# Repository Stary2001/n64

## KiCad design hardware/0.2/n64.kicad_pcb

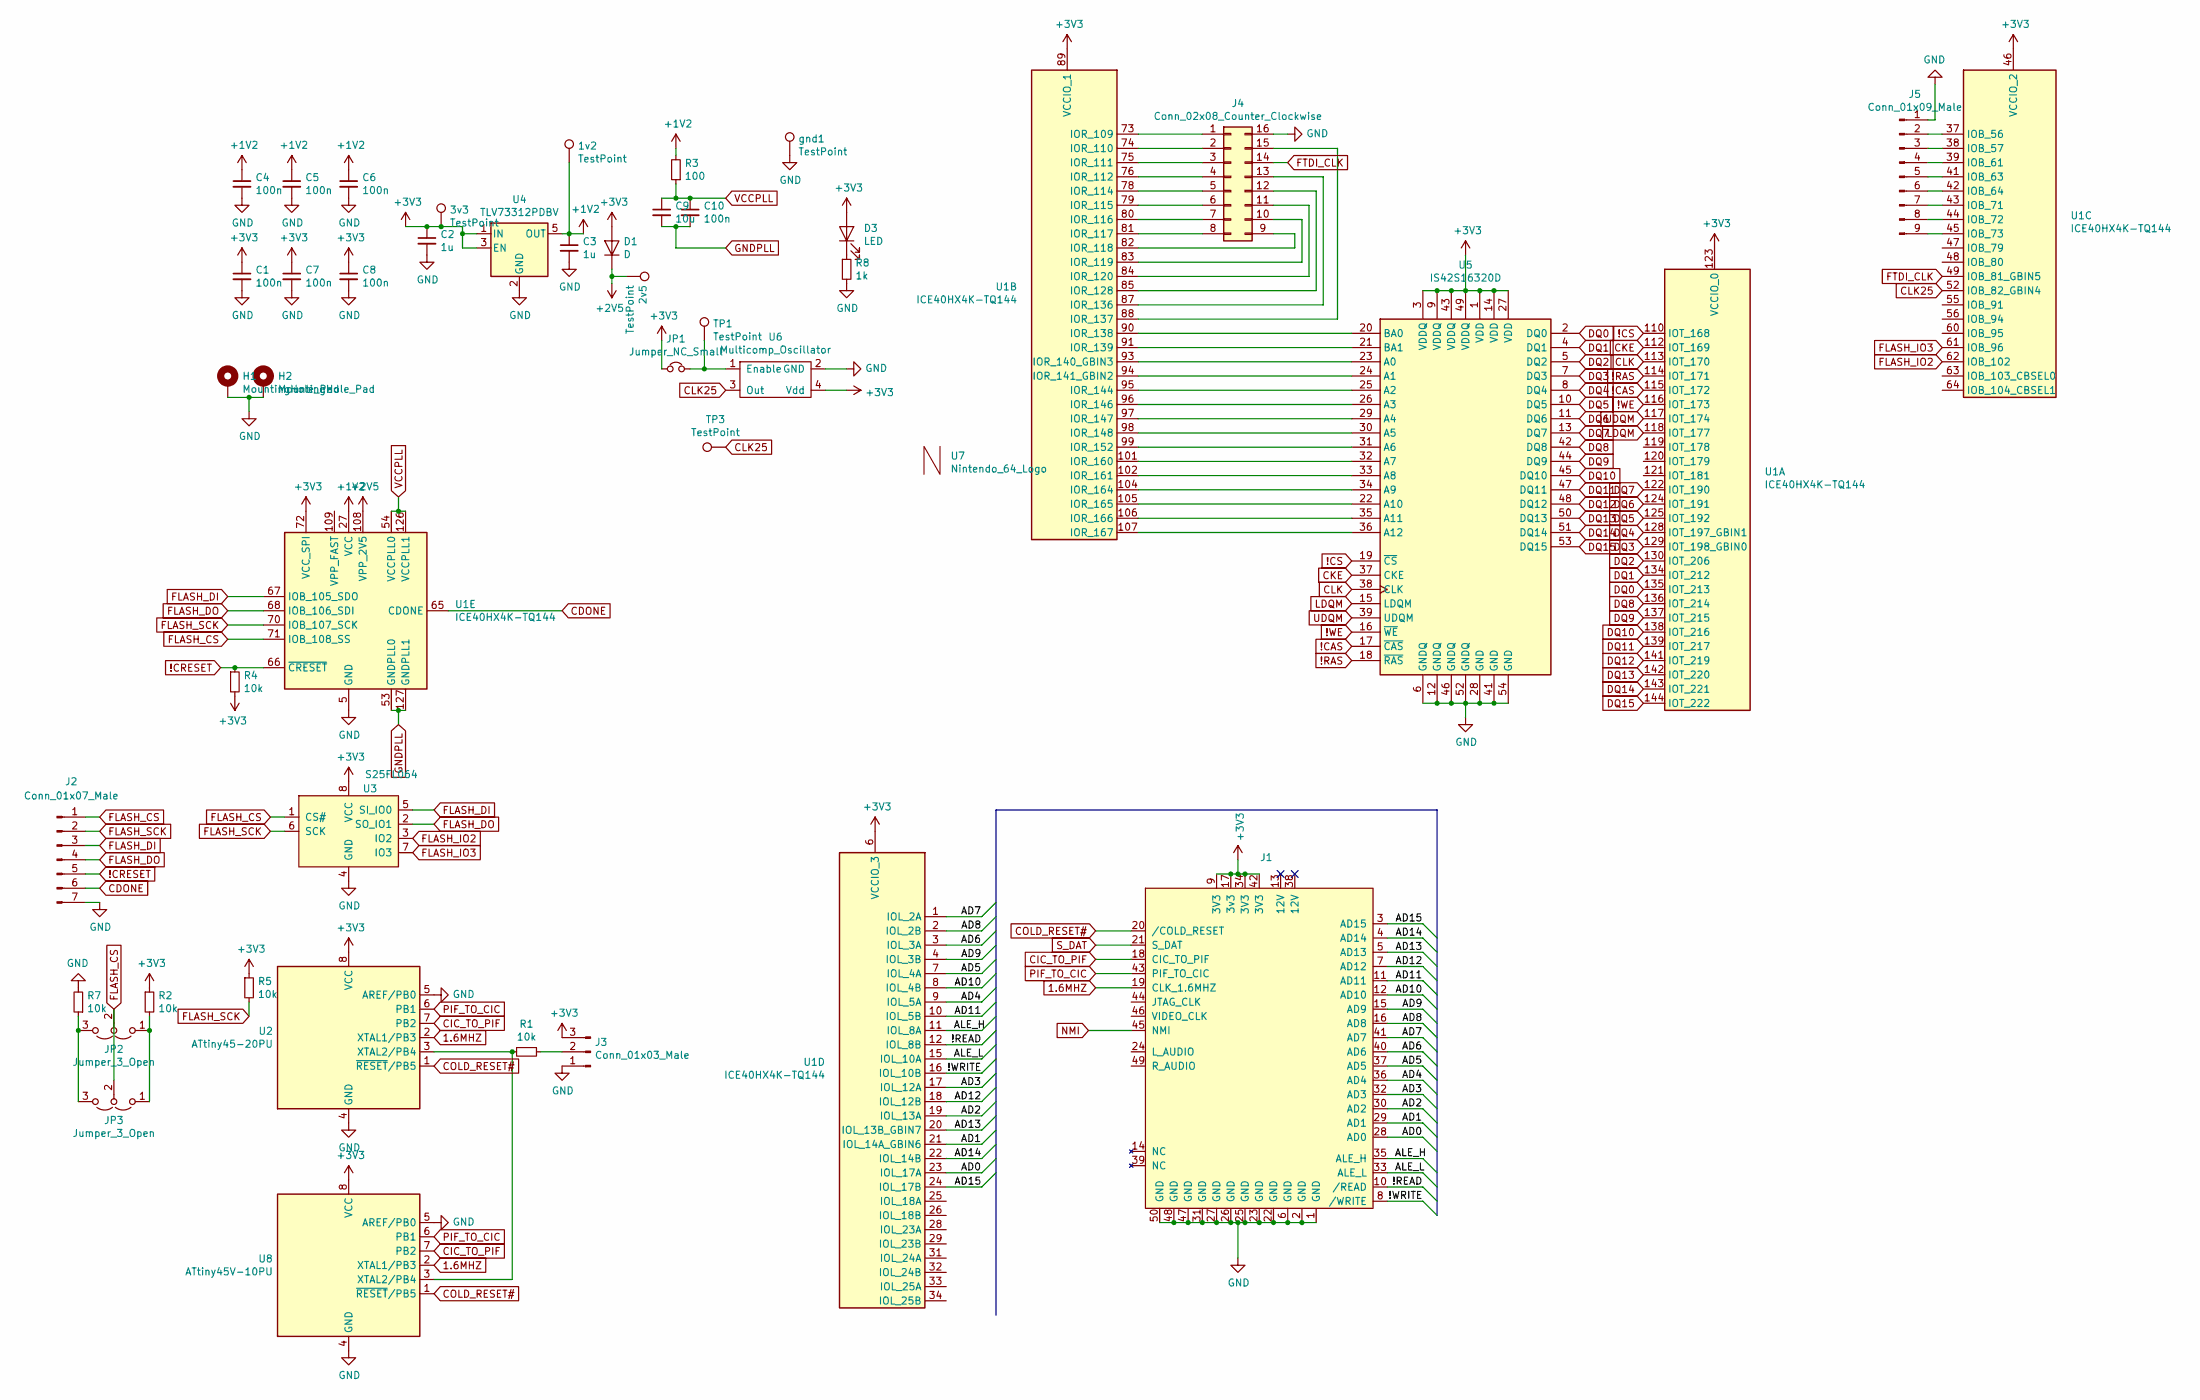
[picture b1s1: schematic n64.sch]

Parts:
1v2, 2v5, 3v3: TestPoint; TestPoint_Pad_D2.5mm
C1, C4, C5, C6, C7, C8, C10: 100n; R_0603_1608Metric_Pad1.05x0.95mm_HandSolder
C2, C3: 1u; R_0603_1608Metric_Pad1.05x0.95mm_HandSolder
C9: 10u; R_0603_1608Metric_Pad1.05x0.95mm_HandSolder
D1: D; D_SOD-123
D3: LED; LED_0603_1608Metric_Pad1.05x0.95mm_HandSolder
H1, H2: MountingHole_Pad; MountingHole_2.7mm_M2.5_Pad
J1: Nintendo_64_Cartridge
J2: Conn_01x07_Male; PinHeader_1x07_P2.54mm_Vertical
J3: Conn_01x03_Male; PinHeader_1x03_P2.54mm_Vertical
J4: Conn_02x08_Counter_Clockwise; IDC-Header_2x08_P2.54mm_Vertical
J5: Conn_01x09_Male; PinHeader_1x09_P2.54mm_Vertical
JP1: Jumper_NC_Small; SolderJumper-2_P1.3mm_Bridged_RoundedPad1.0x1.5mm
JP2: Jumper_3_Open; PinHeader_1x03_P2.54mm_Vertical
JP3: Jumper_3_Open; SolderJumper-3_P1.3mm_Open_Pad1.0x1.5mm_NumberLabels
R1, R2, R4, R5, R7: 10k; R_0603_1608Metric_Pad1.05x0.95mm_HandSolder
R3: 100; R_0603_1608Metric_Pad1.05x0.95mm_HandSolder
R8: 1k; R_0603_1608Metric_Pad1.05x0.95mm_HandSolder
TP1, TP3: TestPoint; TestPoint_Pad_D1.5mm
U1: ICE40HX4K-TQ144; TQFP-144_20x20mm_P0.5mm
U2: ATtiny45-20PU; DIP-8_W7.62mm
U3: S25FL064; SOIC-8_5.23x5.23mm_P1.27mm
U4: TLV73312PDBV; SOT-23-5
U5: IS42S16320D; TSOP-II-54_22.2x10.16mm_P0.8mm
U6: Multicomp_Oscillator; Oscillator_SMD_Abracon_ASE-4Pin_3.2x2.5mm
U7: Nintendo_64_Logo
U8: ATtiny45V-10PU; SOIC-8_5.23x5.23mm_P1.27mm
gnd1: TestPoint; TestPoint_Pad_D2.5mm

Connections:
1.6MHZ: J1.19 (CLK_1.6MHZ), U2.2 (XTAL1/PB3), U8.2 (XTAL1/PB3)
!CAS: U1.115 (IOT_172), U5.17 (~CAS)
!CRESET: J2.5, R4.1, U1.66 (~CRESET)
!CS: U1.110 (IOT_168), U5.19 (~CS)
!RAS: U1.114 (IOT_171), U5.18 (~RAS)
!WE: U1.116 (IOT_173), U5.16 (~WE)
+1V2: 1v2.1, C3.1, C4.1, C5.1, C6.1, R3.2, U1.27 (VCC), U1.40 (VCC), U1.92 (VCC), U1.111 (VCC), U4.5 (OUT)
+2V5: 2v5.1, D1.1 (K), U1.108 (VPP_2V5)
+3V3: 3v3.1, C1.1, C2.1, C7.1, C8.1, D1.2 (A), D3.2 (A), J1.9 (3V3), J1.17 (3v3), J1.34 (3V3), J1.42 (3V3), J3.3, JP1.1, R2.1, R4.2, R5.1, U1.6 (VCCIO_3), U1.30 (VCCIO_3), U1.46 (VCCIO_2), U1.57 (VCCIO_2), U1.72 (VCC_SPI), U1.89 (VCCIO_1), U1.100 (VCCIO_1), U1.123 (VCCIO_0), U1.131 (VCCIO_0), U2.8 (VCC), U3.8 (VCC), U4.1 (IN), U4.3 (EN), U5.1 (VDD), U5.3 (VDDQ), U5.9 (VDDQ), U5.14 (VDD), U5.27 (VDD), U5.43 (VDDQ), U5.49 (VDDQ), U6.4 (Vdd), U8.8 (VCC)
/!READ: J1.10 (/READ), U1.12 (IOL_8B)
/!WRITE: J1.8 (/WRITE), U1.16 (IOL_10B)
/AD0: J1.28 (AD0), U1.23 (IOL_17A)
/AD1: J1.29 (AD1), U1.21 (IOL_14A_GBIN6)
/AD2: J1.30 (AD2), U1.19 (IOL_13A)
/AD3: J1.32 (AD3), U1.17 (IOL_12A)
/AD4: J1.36 (AD4), U1.9 (IOL_5A)
/AD5: J1.37 (AD5), U1.7 (IOL_4A)
/AD6: J1.40 (AD6), U1.3 (IOL_3A)
/AD7: J1.41 (AD7), U1.1 (IOL_2A)
/AD8: J1.16 (AD8), U1.2 (IOL_2B)
/AD9: J1.15 (AD9), U1.4 (IOL_3B)
/AD10: J1.12 (AD10), U1.8 (IOL_4B)
/AD11: J1.11 (AD11), U1.10 (IOL_5B)
/AD12: J1.7 (AD12), U1.18 (IOL_12B)
/AD13: J1.5 (AD13), U1.20 (IOL_13B_GBIN7)
/AD14: J1.4 (AD14), U1.22 (IOL_14B)
/AD15: J1.3 (AD15), U1.24 (IOL_17B)
/ALE_H: J1.35 (ALE_H), U1.11 (IOL_8A)
/ALE_L: J1.33 (ALE_L), U1.15 (IOL_10A)
CDONE: J2.6, U1.65 (CDONE)
CIC_TO_PIF: J1.18 (CIC_TO_PIF), U2.7 (PB2), U8.7 (PB2)
CKE: U1.112 (IOT_169), U5.37 (CKE)
CLK: U1.113 (IOT_170), U5.38 (CLK)
CLK25: TP3.1, U1.52 (IOB_82_GBIN4), U6.3 (Out)
COLD_RESET#: J1.20 (/COLD_RESET), U2.1 (~RESET~/PB5), U8.1 (~RESET~/PB5)
DQ0: U1.135 (IOT_213), U5.2 (DQ0)
DQ1: U1.134 (IOT_212), U5.4 (DQ1)
DQ2: U1.130 (IOT_206), U5.5 (DQ2)
DQ3: U1.129 (IOT_198_GBIN0), U5.7 (DQ3)
DQ4: U1.128 (IOT_197_GBIN1), U5.8 (DQ4)
DQ5: U1.125 (IOT_192), U5.10 (DQ5)
DQ6: U1.124 (IOT_191), U5.11 (DQ6)
DQ7: U1.122 (IOT_190), U5.13 (DQ7)
DQ8: U1.136 (IOT_214), U5.42 (DQ8)
DQ9: U1.137 (IOT_215), U5.44 (DQ9)
DQ10: U1.138 (IOT_216), U5.45 (DQ10)
DQ11: U1.139 (IOT_217), U5.47 (DQ11)
DQ12: U1.141 (IOT_219), U5.48 (DQ12)
DQ13: U1.142 (IOT_220), U5.50 (DQ13)
DQ14: U1.143 (IOT_221), U5.51 (DQ14)
DQ15: U1.144 (IOT_222), U5.53 (DQ15)
FLASH_CS: J2.1, JP2.2 (C), JP3.2 (C), U1.71 (IOB_108_SS), U3.1 (CS#)
FLASH_DI: J2.3, U1.67 (IOB_105_SDO), U3.5 (SI_IO0)
FLASH_DO: J2.4, U1.68 (IOB_106_SDI), U3.2 (SO_IO1)
FLASH_IO2: U1.62 (IOB_102), U3.3 (IO2)
FLASH_IO3: U1.61 (IOB_96), U3.7 (IO3)
FLASH_SCK: J2.2, R5.2, U1.70 (IOB_107_SCK), U3.6 (SCK)
FTDI_CLK: J4.14, U1.49 (IOB_81_GBIN5)
GND: C1.2, C2.2, C3.2, C4.2, C5.2, C6.2, C7.2, C8.2, H1.1, H2.1, J1.1 (GND), J1.2 (GND), J1.6 (GND), J1.22 (GND), J1.23 (GND), J1.25 (GND), J1.26 (GND), J1.27 (GND), J1.31 (GND), J1.47 (GND), J1.48 (GND), J1.50 (GND), J2.7, J3.1, J4.16, J5.1, R7.2, R8.2, U1.5 (GND), U1.13 (GND), U1.14 (GND), U1.59 (GND), U1.69 (GND), U1.86 (GND), U1.103 (GND), U1.132 (GND), U1.140 (GND), U2.4 (GND), U2.5 (AREF/PB0), U3.4 (GND), U4.2 (GND), U5.6 (GNDQ), U5.12 (GNDQ), U5.28 (GND), U5.41 (GND), U5.46 (GNDQ), U5.52 (GNDQ), U5.54 (GND), U6.2 (GND), U8.4 (GND), U8.5 (AREF/PB0), gnd1.1
GNDPLL: C9.2, C10.2, U1.53 (GNDPLL0), U1.127 (GNDPLL1)
LDQM: U1.118 (IOT_177), U5.15 (LDQM)
NMI: J1.45 (NMI)
unnamed: D3.1 (K), R8.1
unnamed: J3.2, R1.1
unnamed: J4.1, U1.73 (IOR_109)
unnamed: J4.2, U1.74 (IOR_110)
unnamed: J4.3, U1.75 (IOR_111)
unnamed: J4.4, U1.76 (IOR_112)
unnamed: J4.5, U1.78 (IOR_114)
unnamed: J4.6, U1.79 (IOR_115)
unnamed: J4.7, U1.80 (IOR_116)
unnamed: J4.8, U1.81 (IOR_117)
unnamed: J4.9, U1.82 (IOR_118)
unnamed: J4.10, U1.83 (IOR_119)
unnamed: J4.11, U1.84 (IOR_120)
unnamed: J4.12, U1.85 (IOR_128)
unnamed: J4.13, U1.87 (IOR_136)
unnamed: J4.15, U1.88 (IOR_137)
unnamed: J5.2, U1.37 (IOB_56)
unnamed: J5.3, U1.38 (IOB_57)
unnamed: J5.4, U1.39 (IOB_61)
unnamed: J5.5, U1.41 (IOB_63)
unnamed: J5.6, U1.42 (IOB_64)
unnamed: J5.7, U1.43 (IOB_71)
unnamed: J5.8, U1.44 (IOB_72)
unnamed: J5.9, U1.45 (IOB_73)
unnamed: JP1.2, TP1.1, U6.1 (Enable)
unnamed: JP2.1 (A), JP3.1 (A), R2.2
unnamed: JP2.3 (B), JP3.3 (B), R7.1
unnamed: R1.2, U2.3 (XTAL2/PB4), U8.3 (XTAL2/PB4)
unnamed: U1.90 (IOR_138), U5.20 (BA0)
unnamed: U1.91 (IOR_139), U5.21 (BA1)
unnamed: U1.93 (IOR_140_GBIN3), U5.23 (A0)
unnamed: U1.94 (IOR_141_GBIN2), U5.24 (A1)
unnamed: U1.95 (IOR_144), U5.25 (A2)
unnamed: U1.96 (IOR_146), U5.26 (A3)
unnamed: U1.97 (IOR_147), U5.29 (A4)
unnamed: U1.98 (IOR_148), U5.30 (A5)
unnamed: U1.99 (IOR_152), U5.31 (A6)
unnamed: U1.101 (IOR_160), U5.32 (A7)
unnamed: U1.102 (IOR_161), U5.33 (A8)
unnamed: U1.104 (IOR_164), U5.34 (A9)
unnamed: U1.105 (IOR_165), U5.22 (A10)
unnamed: U1.106 (IOR_166), U5.35 (A11)
unnamed: U1.107 (IOR_167), U5.36 (A12)
PIF_TO_CIC: J1.43 (PIF_TO_CIC), U2.6 (PB1), U8.6 (PB1)
S_DAT: J1.21 (S_DAT)
UDQM: U1.117 (IOT_174), U5.39 (UDQM)
VCCPLL: C9.1, C10.1, R3.1, U1.54 (VCCPLL0), U1.126 (VCCPLL1)

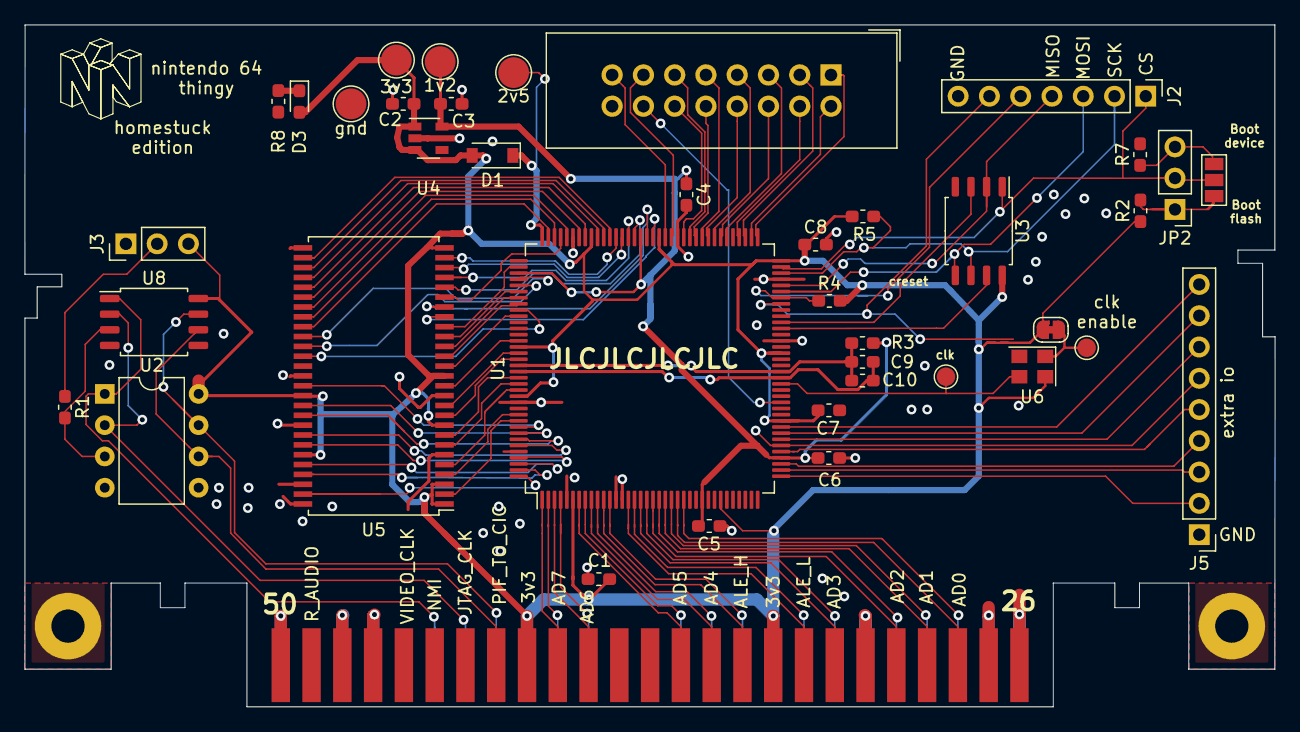
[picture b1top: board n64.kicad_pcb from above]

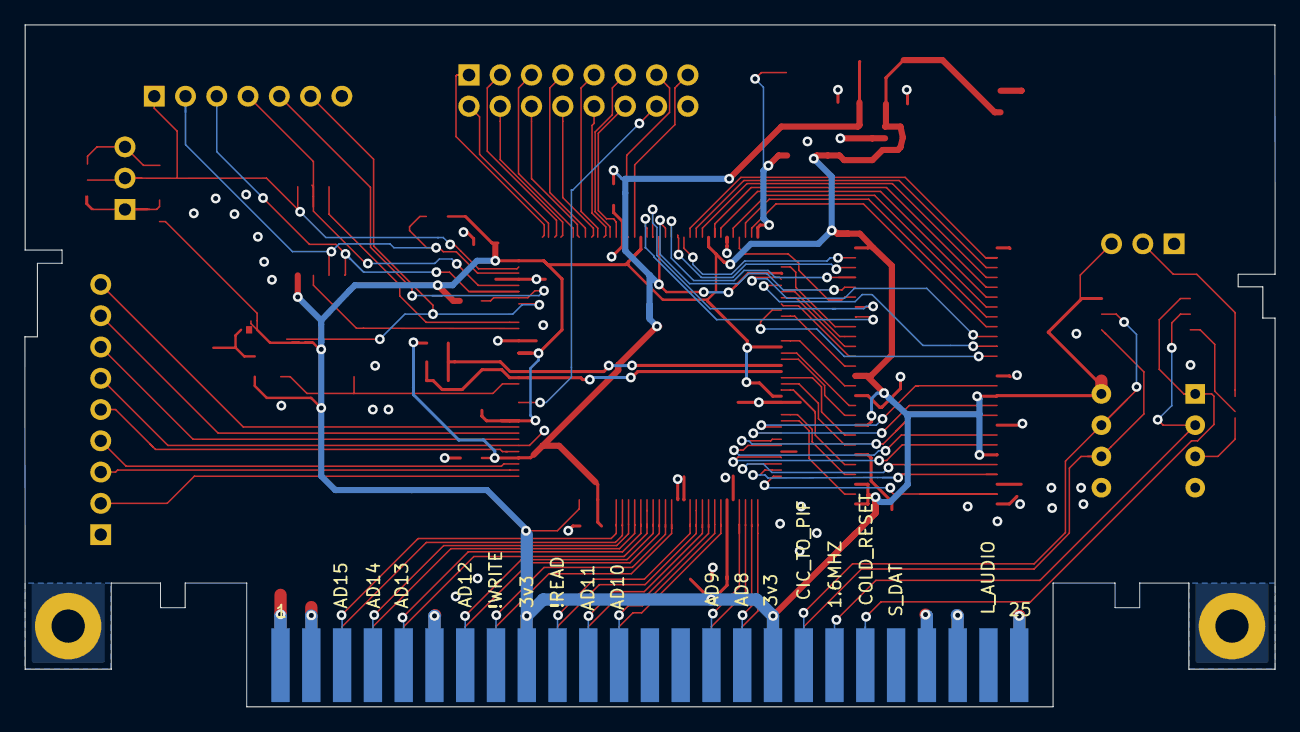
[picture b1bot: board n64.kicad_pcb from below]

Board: 2 copper layers, 101.5 x 55.4 mm, 43 parts (4 on the bottom side), 107 nets.

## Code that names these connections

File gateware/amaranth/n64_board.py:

import os
import subprocess

from amaranth.build import *
from amaranth.vendor import LatticeICE40Platform
from amaranth_boards.resources import *
import tempfile

__all__ = ["N64Platform"]

""""""

"""Resource("ftdi_clk", 0, Pins("49", dir="i"),
            Clock(60e6), Attrs(GLOBAL=True, IO_STANDARD="SB_LVCMOS")
        ),

        SDRAMResource(0,
            clk="113", cke="112", cs="110", we="116", ras="114", cas="115",
            ba="90 91", a="93 94 95 96 97 98 99 101 102 104 105 106 107",
            dq="135 134 130 129 128 125 124 122 138 139 141 142 143 144",
            dqm="118 117", attrs=Attrs(IO_STANDARD="SB_LVCMOS")
        ),

        # todo: check mosi/miso ordering...
        *SPIFlashResources(0,
            cs="71", clk="70", mosi="67", miso="68", wp="62", hold="61",
            attrs=Attrs(IO_STANDARD="SB_LVCMOS")
        ),"""

"""

Resource("ftdi", 0, 
    Subsignal("data", Pins("73 74 75 76 78 79 80 81", dir="io")),
    Subsignal("rxf", Pins("82", dir="i")), #C0
    Subsignal("txe", Pins("83", dir="i")), #C1
    Subsignal("rd", Pins("84", dir="o")), #C2
    Subsignal("wr", Pins("85", dir="o")), #C3
    Subsignal("siwua", Pins("87", dir="o")), #C4
    #Subsignal("clkout", Pins("49")), #C5
    Subsignal("oe", Pins("88", dir="o")), #C6
),"""

class N64Platform(LatticeICE40Platform):
    device      = "iCE40HX4K"
    package     = "TQ144"
    default_clk = "clk25"

    resources   = [
        Resource("clk25", 0, Pins("52", dir="i"),
            Clock(25e6), Attrs(GLOBAL=True, IO_STANDARD="SB_LVCMOS")
        ),

        *SPIFlashResources(0, clk="70", cipo="68", copi="67", cs_n="71", wp_n="62", hold_n="61"),

        #Resource("extra_io", 0, Pins("37 38 39 41 42 43 44 45", dir="io")),
        Resource("io", 0, Pins("37", dir="io")), # pin 2
        Resource("io", 1, Pins("38", dir="io")),
        Resource("io", 2, Pins("39", dir="io")),
        Resource("io", 3, Pins("41", dir="io")),
        Resource("io", 4, Pins("42", dir="io")), # pin 6
        Resource("io", 5, Pins("43", dir="io")), # pin 7
        Resource("io", 6, Pins("44", dir="io")), # pin 8
        Resource("io", 7, Pins("45", dir="io")), # pin 9

        Resource("io", 15, Pins("73", dir="io")),
        Resource("io", 14, Pins("75", dir="io")),
        Resource("io", 13, Pins("78", dir="io")),
        Resource("io", 12, Pins("80", dir="io")),
        Resource("io", 11, Pins("82", dir="io")),
        Resource("io", 10, Pins("84", dir="io")),
        Resource("io", 9, Pins("87", dir="io")),
        Resource("io", 8, Pins("88", dir="io")),

        Resource("n64", 0, 
            Subsignal("ad", Pins("23 21 19 17 9 7 3 1 2 4 8 10 18 20 22 24", dir="io")),
            Subsignal("read", Pins("12", dir="i")),
            Subsignal("write", Pins("16", dir="i")),
            Subsignal("ale_l", Pins("15", dir="i")),
            Subsignal("ale_h", Pins("11", dir="i")),
            Subsignal("cold_reset", Pins("83", dir="i")),
            Subsignal("nmi", PinsN("81", dir="i")),
        ),

        SDRAMResource(0,
            clk = "113",
            cke = "112",
            cs_n = "110",
            we_n = "116",
            ras_n = "114",
            cas_n = "115",

            ba = "90 91",
            a = "93 94 95 96 97 98 99 101 102 104 105 106 107",
            dq = "135 134 130 129 128 125 124 122 136 137 138 139 141 142 143 144",
            dqm = "118 117",

            attrs = Attrs(IO_STANDARD = "SB_LVCMOS")
        ),
    ]

    connectors  = [
    ]

    def toolchain_program(self, products, name):
        iceprog = os.environ.get("ICEPROG", "iceprog")
        with products.extract("{}.bin".format(name)) as bitstream_filename:
            subprocess.check_call(f"glasgow run program-ice40-flash -V 3.3 -f 100 --cs A0 --sck A1 --io A2,A3,A6,A7 --done A4 --reset A5 erase-program -P 64 -S 4096 -f {bitstream_filename} 0", shell=True)
            subprocess.check_call(f"glasgow run program-ice40-flash -V 3.3 -f 100 --cs A0 --sck A1 --io A2,A3,A6,A7 --done A4 --reset A5 erase-program -P 64 -S 4096 -f {bitstream_filename} 0", shell=True)
            subprocess.check_call(f"glasgow voltage A 0", shell=True)

if __name__ == "__main__":
    from .test.blinky import *
    N64Platform().build(Blinky(), do_program=True)

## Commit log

2020-04-04 Initial version??
2020-04-20 probably close enough to "homestuck edition"
2020-04-22 move to subdir
2020-04-22 copy
2020-04-22 some changes
2020-04-22 add gateware
2020-04-29 initial nmigen cart bus stuff
2020-04-29 update litex soc
2020-04-29 actually use io register
2020-05-01 added log skip
2020-05-03 rename again, add sim
2020-05-08 whoops
2020-06-21 ship it
2020-06-22 fix sim
2020-06-24 try to add more sim methods, but the sdram sim model is bad
2020-06-24 alter sim model slightly
2020-06-24 Revert "alter sim model slightly"
    This reverts commit fc9f9fb66584bb57c6e717bdb6e4553d02a9546d.
2020-06-27 start working on cpu stuff
2020-06-28 working C on hardware!
2020-06-28 oops
2021-06-04 hopefully ok
2025-05-29 Port to amaranth
2025-05-30 Update sim, break sdram controller, etc
